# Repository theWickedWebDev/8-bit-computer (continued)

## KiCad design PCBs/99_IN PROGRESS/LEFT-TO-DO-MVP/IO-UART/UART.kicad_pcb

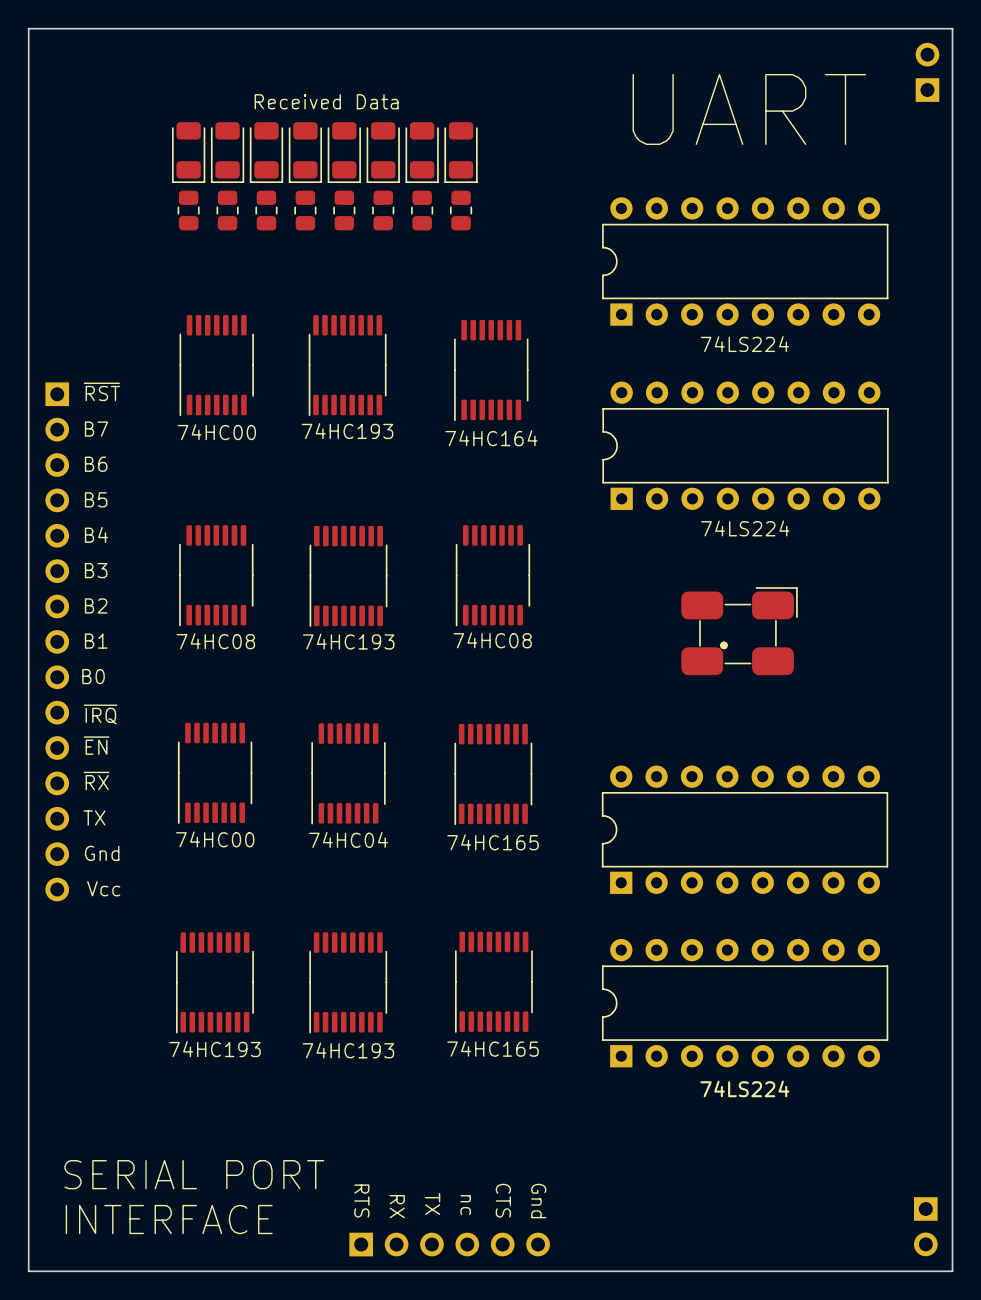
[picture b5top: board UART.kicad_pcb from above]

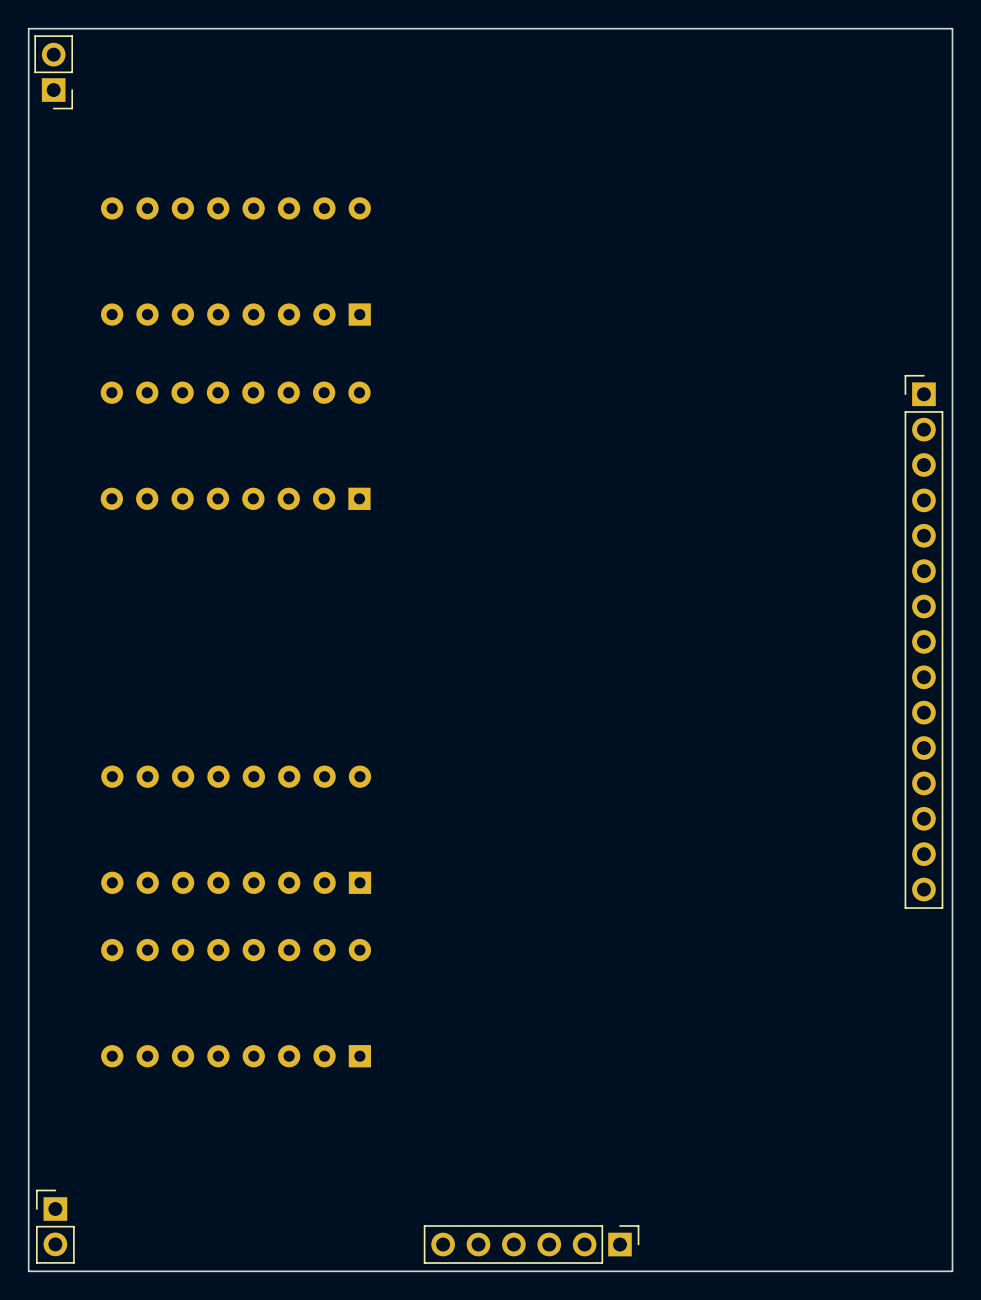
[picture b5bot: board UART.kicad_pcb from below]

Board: 4 copper layers, 66.3 x 89.2 mm, 37 parts (4 on the bottom side), 66 nets, no tracks yet.

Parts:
D1, D2, D3, D4, D5, D6, D7, D8: LED; LED_1206_3216Metric
J1: Conn_01x06; PinHeader_1x06_P2.54mm_Vertical
J2: Conn_01x15; PinHeader_1x15_P2.54mm_Vertical
J3, J4: Conn_01x02; PinHeader_1x02_P2.54mm_Vertical
R1, R2, R3, R4, R5, R6, R7, R8: 1kohm; R_0805_2012Metric
U1, U2, U3, U4: 74LS193; TSSOP-16_4.4x5mm_P0.65mm
U5, U14: 74LS08; TSSOP-14_4.4x5mm_P0.65mm
U6, U7: 74LS00; TSSOP-14_4.4x5mm_P0.65mm
U8: 74LS04; TSSOP-14_4.4x5mm_P0.65mm
U9: 74HC164; TSSOP-14_4.4x5mm_P0.65mm
U10, U11: 74LS165; TSSOP-16_4.4x5mm_P0.65mm
U12, U13, U15, U18: 74LS224; DIP-16_W7.62mm
Y1: Crystal_GND24; CFPS-72 SMD Clock

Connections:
/READ: U12.1 (OE), U12.15 (UNCK), U13.1 (OE), U13.15 (UNCK), U14.3
/TX0: D8.2 (A), U9.3 (Q0), U12.4 (D0)
/TX1: D7.2 (A), U9.4 (Q1), U12.5 (D1)
/TX2: D6.2 (A), U9.5 (Q2), U12.6 (D2)
/TX3: D5.2 (A), U9.6 (Q3), U12.7 (D3)
/TX4: D4.2 (A), U9.10 (Q4), U13.4 (D0)
/TX5: D3.2 (A), U9.11 (Q5), U13.5 (D1)
/TX6: D2.2 (A), U9.12 (Q6), U13.6 (D2)
/TX7: D1.2 (A), U9.13 (Q7), U13.7 (D3)
/TX_CLOCK: U2.7 (QD), U4.5 (UP), U6.10, U10.2 (CP), U11.2 (CP)
/TX_START: U4.11 (~LOAD), U6.3, U6.5, U10.1 (~PL), U11.1 (~PL), U15.1 (OE), U15.15 (UNCK), U18.1 (OE), U18.15 (UNCK)
/WRITE: U3.14 (CLR), U7.3, U7.4, U12.3 (LDCK), U13.3 (LDCK)
BUS0: J2.2, U12.13 (Q0), U15.4 (D0)
BUS1: J2.3, U12.12 (Q1), U15.5 (D1)
BUS2: J2.4, U12.11 (Q2), U15.6 (D2)
BUS3: J2.5, U12.10 (Q3), U15.7 (D3)
BUS4: J2.6, U13.13 (Q0), U18.4 (D0)
BUS5: J2.7, U13.12 (Q1), U18.5 (D1)
BUS6: J2.8, U13.11 (Q2), U18.6 (D2)
BUS7: J2.9, U13.10 (Q3), U18.7 (D3)
EN: U5.2, U8.6, U14.1
GND: J1.6, J2.14, R1.2, R2.2, R3.2, R4.2, R5.2, R6.2, R7.2, R8.2, U1.1 (B), U1.8 (GND), U1.10 (C), U1.14 (CLR), U2.1 (B), U2.8 (GND), U2.9 (D), U2.10 (C), U2.14 (CLR), U2.15 (A), U3.1 (B), U3.8 (GND), U3.9 (D), U3.10 (C), U3.15 (A), U4.1 (B), U4.8 (GND), U4.9 (D), U4.14 (CLR), U5.7 (GND), U5.12, U5.13, U6.7 (GND), U6.12, U6.13, U7.7 (GND), U7.9, U7.10, U7.12, U7.13, U8.7 (GND), U8.13, U9.7 (GND), U10.5 (D6), U10.8 (GND), U10.15 (~CE), U11.8 (GND), U11.15 (~CE), U12.8 (GND), U13.8 (GND), U14.7 (GND), U14.12, U14.13, U15.8 (GND), U18.8 (GND), Y1.2
unnamed: D1.1 (K), R1.1
unnamed: D2.1 (K), R2.1
unnamed: D3.1 (K), R3.1
unnamed: D4.1 (K), R4.1
unnamed: D5.1 (K), R5.1
unnamed: D6.1 (K), R6.1
unnamed: D7.1 (K), R7.1
unnamed: D8.1 (K), R8.1
unnamed: U1.4 (DOWN), U3.7 (QD), U9.8 (CP)
unnamed: U1.11 (~LOAD), U7.2, U7.6
unnamed: U1.13 (~BO), U7.1
unnamed: U4.12 (~CO), U6.4
unnamed: U5.5, U18.2 (IR)
unnamed: U5.8, U8.11
unnamed: U6.2, U6.8
unnamed: U8.1, U14.8
unnamed: U10.10 (DS), U11.9 (Q7)
unnamed: U12.2 (IR), U14.4
unnamed: U12.14 (OR), U14.9
unnamed: U13.2 (IR), U14.5
unnamed: U13.14 (OR), U14.10
unnamed: U5.4, U15.2 (IR)
unnamed: U5.9, U15.14 (OR)
unnamed: U5.10, U18.14 (OR)
RECEIVE_BYTE: J2.12, U8.4, U14.2
RX0: U10.4 (D5), U15.13 (Q0)
RX1: U10.3 (D4), U15.12 (Q1)
RX2: U10.14 (D3), U15.11 (Q2)
RX3: U10.13 (D2), U15.10 (Q3)
RX4: U10.12 (D1), U18.13 (Q0)
RX5: U10.11 (D0), U18.12 (Q1)
RX6: U11.6 (D7), U18.11 (Q2)
RX7: U11.5 (D6), U18.10 (Q3)
SER_CTS: J1.5, U14.6
SER_RTS: J1.1, U6.9, U8.10
SER_RX: J1.2, U10.9 (Q7)
SER_TX: J1.3, U7.5, U9.1 (DSA)
TF_DATA_READ: U6.1, U6.6
TRANSMIT_BYTE: J2.13, U5.1, U5.3, U8.8, U15.3 (LDCK), U18.3 (LDCK)
UART_CLOCK: U2.5 (UP), U3.5 (UP), Y1.3
VCC: J2.15, U1.5 (UP), U1.9 (D), U1.15 (A), U1.16 (VCC), U2.4 (DOWN), U2.11 (~LOAD), U2.16 (VCC), U3.4 (DOWN), U3.11 (~LOAD), U3.16 (VCC), U4.4 (DOWN), U4.10 (C), U4.15 (A), U4.16 (VCC), U5.14 (VCC), U6.14 (VCC), U7.14 (VCC), U8.14 (VCC), U9.2 (DSB), U9.9 (~MR), U9.14 (VCC), U10.6 (D7), U10.16 (VCC), U11.3 (D4), U11.4 (D5), U11.10 (DS), U11.11 (D0), U11.12 (D1), U11.13 (D2), U11.14 (D3), U11.16 (VCC), U12.16 (VCC), U13.16 (VCC), U14.14 (VCC), U15.16 (VCC), U18.16 (VCC), Y1.4
~EN: J2.11, U8.5
~RESET_BUFFERS: J2.1, U12.9 (~CLR), U13.9 (~CLR), U15.9 (~CLR), U18.9 (~CLR)
~RX_IRQ: J2.10, U8.2

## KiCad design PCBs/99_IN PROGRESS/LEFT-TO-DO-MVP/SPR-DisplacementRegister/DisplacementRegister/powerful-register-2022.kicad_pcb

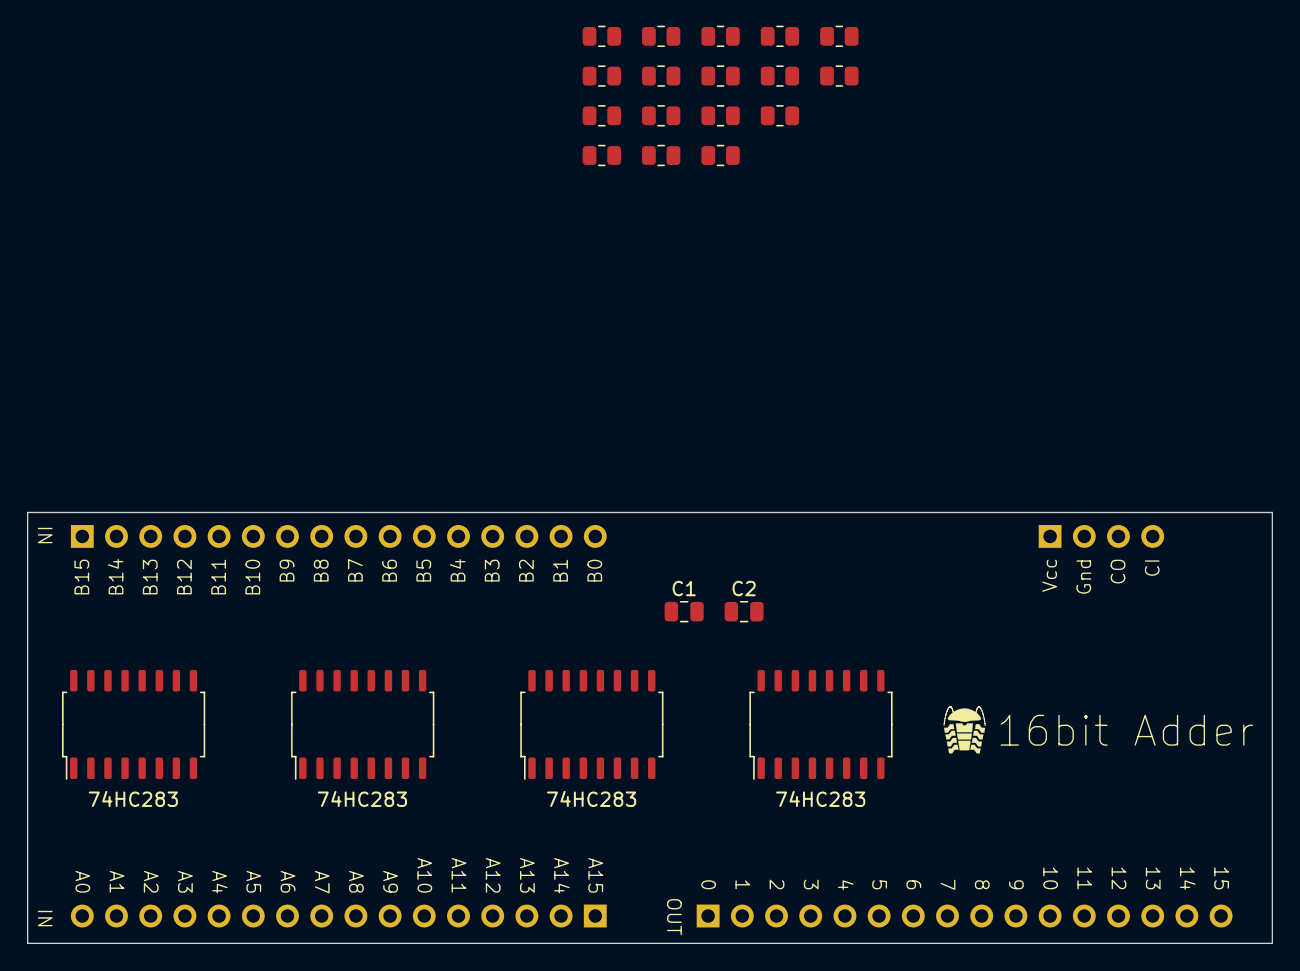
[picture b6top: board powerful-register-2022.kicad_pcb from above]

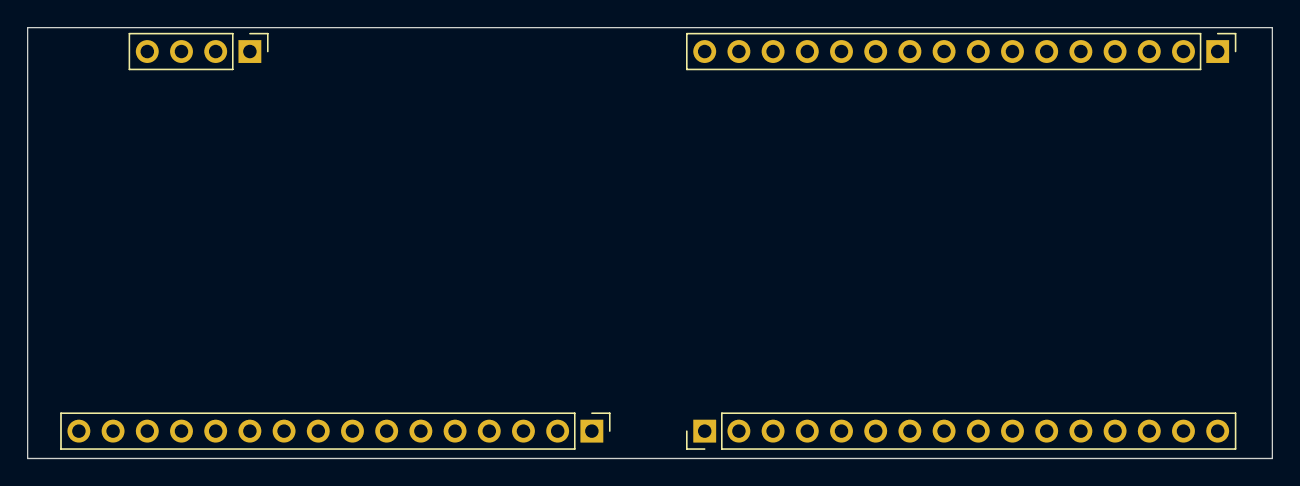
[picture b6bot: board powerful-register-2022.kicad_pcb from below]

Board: 4 copper layers, 92.5 x 32.0 mm, 27 parts (4 on the bottom side), 55 nets, no tracks yet.

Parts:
C1, C2: C; C_0805_2012Metric
J1: Conn_01x06; PinHeader_1x04_P2.54mm_Vertical
J2, J3, J4: Conn_01x16; PinHeader_1x16_P2.54mm_Vertical
R1, R2, R3, R4, R5, R6, R7, R8, R9, R10, R11, R12, R13, R14, R15, R16, R17: R_Small_US; R_0805_2012Metric
U1, U2, U3, U4: 74LS283; SOIC-16_4.55x10.3mm_P1.27mm

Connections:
A0: J2.16, U1.5 (A1)
A1: J2.15, U1.3 (A2)
A2: J2.14, U1.14 (A3)
A3: J2.13, U1.12 (A4)
A4: J2.12, U3.5 (A1)
A5: J2.11, U3.3 (A2)
A6: J2.10, U3.14 (A3)
A7: J2.9, U3.12 (A4)
A8: J2.8, U2.5 (A1)
A9: J2.7, U2.3 (A2)
A10: J2.6, U2.14 (A3)
A11: J2.5, U2.12 (A4)
A12: J2.4, U4.5 (A1)
A13: J2.3, U4.3 (A2)
A14: J2.2, U4.14 (A3)
A15: J2.1, U4.12 (A4)
B0: J4.16, R17.1, U1.6 (B1)
B1: J4.15, R16.1, U1.2 (B2)
B2: J4.14, R15.1, U1.15 (B3)
B3: J4.13, R14.1, U1.11 (B4)
B4: J4.12, R13.1, U3.6 (B1)
B5: J4.11, R12.1, U3.2 (B2)
B6: J4.10, R11.1, U3.15 (B3)
B7: J4.9, R10.1, U3.11 (B4)
B8: J4.8, R9.1, U2.6 (B1)
B9: J4.7, R8.1, U2.2 (B2)
B10: J4.6, R7.1, U2.15 (B3)
B11: J4.5, R6.1, U2.11 (B4)
B12: J4.4, R5.1, U4.6 (B1)
B13: J4.3, R4.1, U4.2 (B2)
B14: J4.2, R2.1, U4.15 (B3)
B15: J4.1, R1.1, U4.11 (B4)
CARRY_IN: J1.4, U1.7 (C0)
CARRY_OUT: J1.3, R3.1, U4.9 (C4)
GND: C1.2, C2.2, J1.2, R1.2, R2.2, R3.2, R4.2, R5.2, R6.2, R7.2, R8.2, R9.2, R10.2, R11.2, R12.2, R13.2, R14.2, R15.2, R16.2, R17.2, U1.8 (GND), U2.8 (GND), U3.8 (GND), U4.8 (GND)
unnamed: U1.9 (C4), U3.7 (C0)
unnamed: U2.7 (C0), U3.9 (C4)
unnamed: U2.9 (C4), U4.7 (C0)
Q0: J3.16, U1.4 (S1)
Q1: J3.15, U1.1 (S2)
Q2: J3.14, U1.13 (S3)
Q3: J3.13, U1.10 (S4)
Q4: J3.12, U3.4 (S1)
Q5: J3.11, U3.1 (S2)
Q6: J3.10, U3.13 (S3)
Q7: J3.9, U3.10 (S4)
Q8: J3.8, U2.4 (S1)
Q9: J3.7, U2.1 (S2)
Q10: J3.6, U2.13 (S3)
Q11: J3.5, U2.10 (S4)
Q12: J3.4, U4.4 (S1)
Q13: J3.3, U4.1 (S2)
Q14: J3.2, U4.13 (S3)
Q15: J3.1, U4.10 (S4)
VCC: C1.1, C2.1, J1.1, U1.16 (VCC), U2.16 (VCC), U3.16 (VCC), U4.16 (VCC)

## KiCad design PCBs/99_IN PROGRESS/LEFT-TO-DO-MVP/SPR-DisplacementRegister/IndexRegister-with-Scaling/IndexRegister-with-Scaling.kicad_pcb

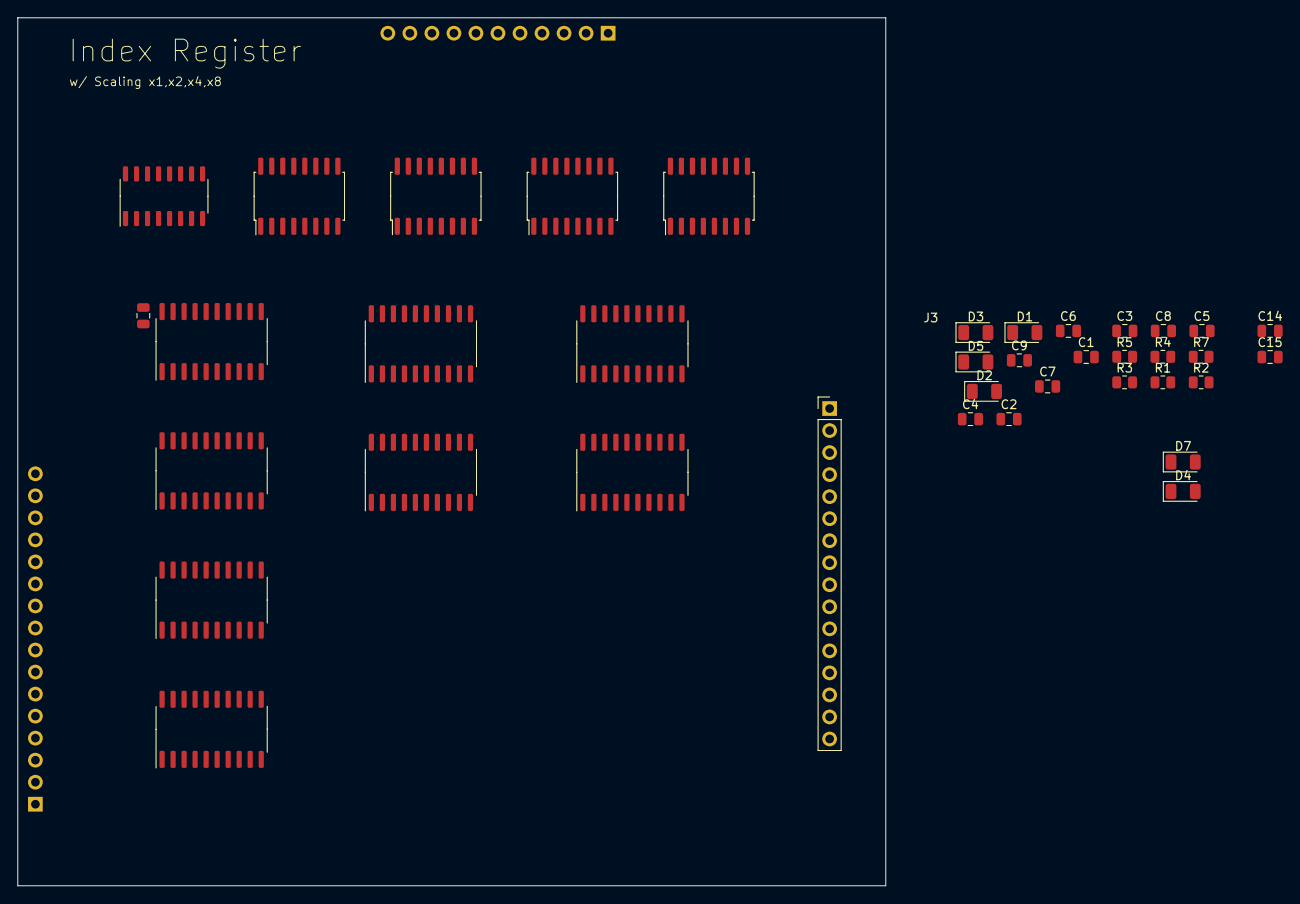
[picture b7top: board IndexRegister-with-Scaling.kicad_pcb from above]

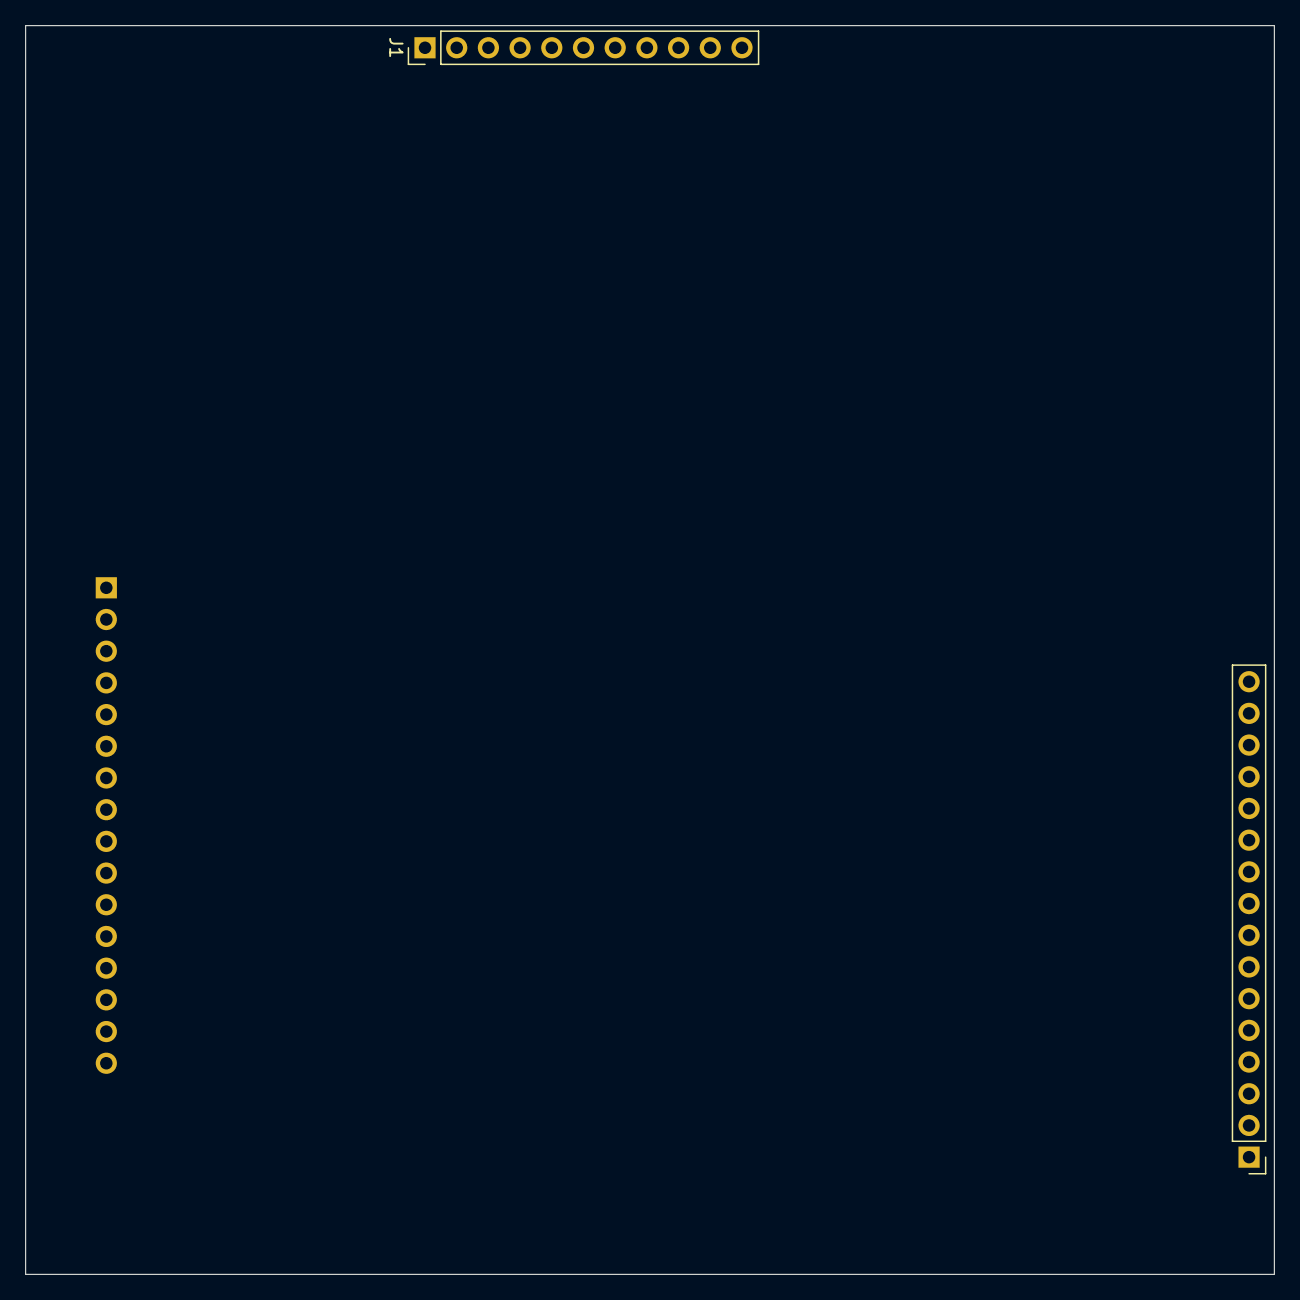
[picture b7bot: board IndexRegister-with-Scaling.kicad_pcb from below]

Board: 2 copper layers, 100.1 x 100.1 mm, 40 parts (2 on the bottom side), 75 nets, no tracks yet.

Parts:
C1, C2, C3, C4, C5, C6, C7, C8, C9: C; C_0805_2012Metric
C13, C14, C15: C_Small; C_0805_2012Metric
D1, D2, D3, D4, D5, D7: LED; LED_1206_3216Metric
J1: Conn_01x11; PinHeader_1x11_P2.54mm_Vertical
J2, J3: Conn_01x16; PinHeader_1x16_P2.54mm_Vertical
R1, R2, R3, R4, R5, R7: R_Small_US; R_0805_2012Metric
U1: 74LS139; SO-16_3.9x9.9mm_P1.27mm
U2, U3, U5, U6, U8, U9, U11, U12: 74LS245; SO-20_5.3x12.6mm_P1.27mm
U14, U15, U16, U17: 74LS193; SO-16_5.3x10.2mm_P1.27mm

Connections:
/Index Register/Q0: U2.2 (A0), U5.3 (A1), U8.4 (A2), U11.5 (A3), U14.3 (QA)
/Index Register/Q1: U2.3 (A1), U5.4 (A2), U8.5 (A3), U11.6 (A4), U14.2 (QB)
/Index Register/Q2: U2.4 (A2), U5.5 (A3), U8.6 (A4), U11.7 (A5), U14.6 (QC)
/Index Register/Q3: U2.5 (A3), U5.6 (A4), U8.7 (A5), U11.8 (A6), U14.7 (QD)
/Index Register/Q4: U2.6 (A4), U5.7 (A5), U8.8 (A6), U11.9 (A7), U15.3 (QA)
/Index Register/Q5: U2.7 (A5), U5.8 (A6), U8.9 (A7), U12.2 (A0), U15.2 (QB)
/Index Register/Q6: U2.8 (A6), U5.9 (A7), U9.2 (A0), U12.3 (A1), U15.6 (QC)
/Index Register/Q7: U2.9 (A7), U6.2 (A0), U9.3 (A1), U12.4 (A2), U15.7 (QD)
/Index Register/Q8: U3.2 (A0), U6.3 (A1), U9.4 (A2), U12.5 (A3), U16.3 (QA)
/Index Register/Q9: U3.3 (A1), U6.4 (A2), U9.5 (A3), U12.6 (A4), U16.2 (QB)
/Index Register/Q10: U3.4 (A2), U6.5 (A3), U9.6 (A4), U12.7 (A5), U16.6 (QC)
/Index Register/Q11: U3.5 (A3), U6.6 (A4), U9.7 (A5), U12.8 (A6), U16.7 (QD)
/Index Register/Q12: U3.6 (A4), U6.7 (A5), U9.8 (A6), U12.9 (A7), U17.3 (QA)
/Index Register/Q13: U3.7 (A5), U6.8 (A6), U9.9 (A7), U17.2 (QB)
/Index Register/Q14: U3.8 (A6), U6.9 (A7), U17.6 (QC)
/Index Register/Q15: U3.9 (A7), U17.7 (QD)
/Scaled Output/~SF1: U1.4 (O0), U2.19 (CE), U3.19 (CE)
/Scaled Output/~SF2: U1.5 (O1), U5.19 (CE), U6.19 (CE)
/Scaled Output/~SF4: U1.6 (O2), U8.19 (CE), U9.19 (CE)
/Scaled Output/~SF8: U1.7 (O3), U11.19 (CE), U12.19 (CE)
A0: J2.16, U14.15 (A)
A1: J2.15, U14.1 (B)
A2: J2.14, U14.10 (C)
A3: J2.13, U14.9 (D)
A4: J2.12, U15.15 (A)
A5: J2.11, U15.1 (B)
A6: J2.10, U15.10 (C)
A7: J2.9, U15.9 (D)
A8: J2.8, U16.15 (A)
A9: J2.7, U16.1 (B)
A10: J2.6, U16.10 (C)
A11: J2.5, U16.9 (D)
A12: J2.4, U17.15 (A)
A13: J2.3, U17.1 (B)
A14: J2.2, U17.10 (C)
A15: J2.1, U17.9 (D)
BO: J1.11, U17.13 (~BO)
CO: J1.10, U17.12 (~CO)
GND: C1.2, C2.2, C3.2, C4.2, C5.2, C6.2, C7.2, C8.2, C9.2, C13.2, C14.2, C15.2, J1.2, R1.2, R2.2, R3.2, R4.2, R5.2, R7.2, U1.8 (GND), U2.10 (GND), U3.10 (GND), U5.2 (A0), U5.10 (GND), U6.10 (GND), U8.2 (A0), U8.3 (A1), U8.10 (GND), U9.10 (GND), U11.2 (A0), U11.3 (A1), U11.4 (A2), U11.10 (GND), U12.10 (GND), U14.8 (GND), U15.8 (GND), U16.8 (GND), U17.8 (GND)
unnamed: D1.1 (K), R1.1
unnamed: D2.1 (K), R2.1
unnamed: D3.1 (K), R3.1
unnamed: D4.1 (K), R4.1
unnamed: D5.1 (K), R5.1
unnamed: D7.1 (K), R7.1
unnamed: U14.12 (~CO), U15.5 (UP)
unnamed: U14.13 (~BO), U15.4 (DOWN)
unnamed: U15.12 (~CO), U16.5 (UP)
unnamed: U15.13 (~BO), U16.4 (DOWN)
unnamed: U16.12 (~CO), U17.5 (UP)
unnamed: U16.13 (~BO), U17.4 (DOWN)
Q0: J3.16, U2.18 (B0), U5.18 (B0), U8.18 (B0), U11.18 (B0)
Q1: J3.15, U2.17 (B1), U5.17 (B1), U8.17 (B1), U11.17 (B1)
Q2: J3.14, U2.16 (B2), U5.16 (B2), U8.16 (B2), U11.16 (B2)
Q3: J3.13, U2.15 (B3), U5.15 (B3), U8.15 (B3), U11.15 (B3)
Q4: J3.12, U2.14 (B4), U5.14 (B4), U8.14 (B4), U11.14 (B4)
Q5: J3.11, U2.13 (B5), U5.13 (B5), U8.13 (B5), U11.13 (B5)
Q6: J3.10, U2.12 (B6), U5.12 (B6), U8.12 (B6), U11.12 (B6)
Q7: J3.9, U2.11 (B7), U5.11 (B7), U8.11 (B7), U11.11 (B7)
Q8: J3.8, U3.18 (B0), U6.18 (B0), U9.18 (B0), U12.18 (B0)
Q9: J3.7, U3.17 (B1), U6.17 (B1), U9.17 (B1), U12.17 (B1)
Q10: J3.6, U3.16 (B2), U6.16 (B2), U9.16 (B2), U12.16 (B2)
Q11: J3.5, U3.15 (B3), U6.15 (B3), U9.15 (B3), U12.15 (B3)
Q12: J3.4, U3.14 (B4), U6.14 (B4), U9.14 (B4), U12.14 (B4)
Q13: J3.3, U3.13 (B5), U6.13 (B5), U9.13 (B5), U12.13 (B5)
Q14: J3.2, U3.12 (B6), U6.12 (B6), U9.12 (B6), U12.12 (B6)
Q15: J3.1, U3.11 (B7), U6.11 (B7), U9.11 (B7), U12.11 (B7)
RESET: J1.3, U14.14 (CLR), U15.14 (CLR), U16.14 (CLR), U17.14 (CLR)
VCC: C1.1, C2.1, C3.1, C4.1, C5.1, C6.1, C7.1, C8.1, C9.1, C13.1, C14.1, C15.1, J1.1, U1.15 (E), U1.16 (VCC), U2.1 (A->B), U2.20 (VCC), U3.1 (A->B), U3.20 (VCC), U5.1 (A->B), U5.20 (VCC), U6.1 (A->B), U6.20 (VCC), U8.1 (A->B), U8.20 (VCC), U9.1 (A->B), U9.20 (VCC), U11.1 (A->B), U11.20 (VCC), U12.1 (A->B), U12.20 (VCC), U14.16 (VCC), U15.16 (VCC), U16.16 (VCC), U17.16 (VCC)
~INDEX_C0: D4.2 (A), J1.7, U1.3 (A1)
~INDEX_C1: D5.2 (A), J1.8, U1.2 (A0)
~INDEX_DEC: D1.2 (A), J1.4, U14.4 (DOWN)
~INDEX_INC: D2.2 (A), J1.5, U14.5 (UP)
~INDEX_LOAD: D3.2 (A), J1.6, U14.11 (~LOAD), U15.11 (~LOAD), U16.11 (~LOAD), U17.11 (~LOAD)
~INDEX_OE: D7.2 (A), J1.9, U1.1 (E)

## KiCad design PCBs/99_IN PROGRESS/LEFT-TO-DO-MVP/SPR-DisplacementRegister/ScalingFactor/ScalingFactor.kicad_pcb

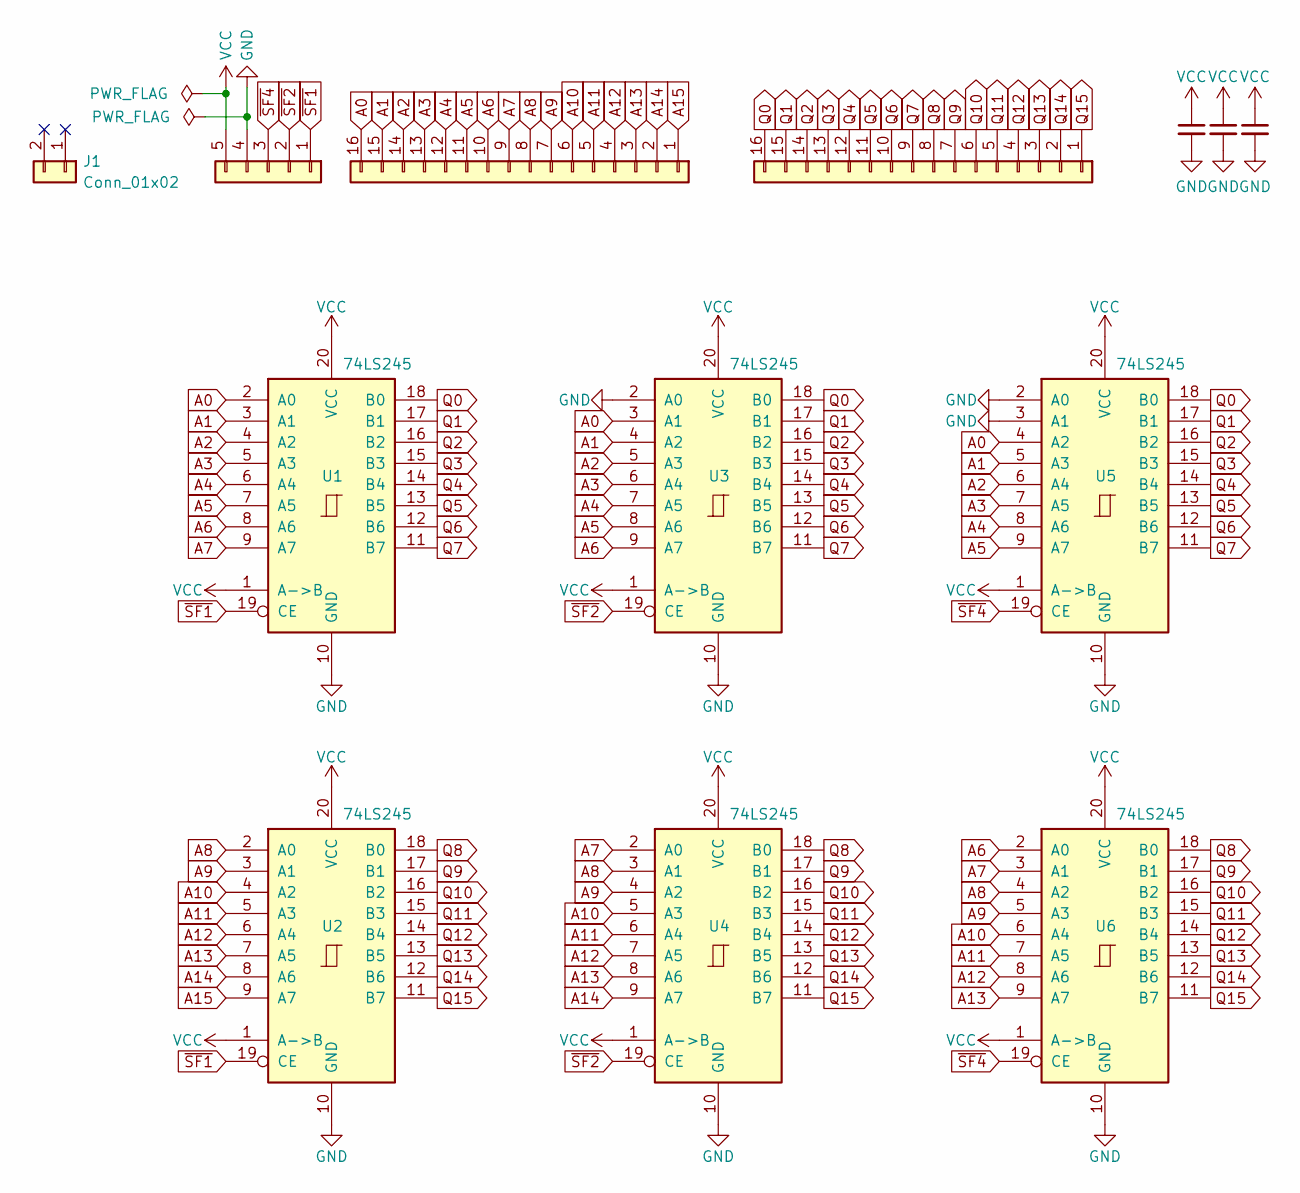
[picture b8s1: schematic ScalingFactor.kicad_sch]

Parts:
C1, C2, C3: C_Small; C_0805_2012Metric
J1: Conn_01x02; PinHeader_1x02_P2.54mm_Vertical
J2: Conn_01x05; PinHeader_1x05_P2.54mm_Vertical
J3, J4: Conn_01x16; PinHeader_1x16_P2.54mm_Vertical
U1, U2, U3, U4, U5, U6: 74LS245; SO-20_5.3x12.6mm_P1.27mm

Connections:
A0: J3.16, U1.2 (A0), U3.3 (A1), U5.4 (A2)
A1: J3.15, U1.3 (A1), U3.4 (A2), U5.5 (A3)
A2: J3.14, U1.4 (A2), U3.5 (A3), U5.6 (A4)
A3: J3.13, U1.5 (A3), U3.6 (A4), U5.7 (A5)
A4: J3.12, U1.6 (A4), U3.7 (A5), U5.8 (A6)
A5: J3.11, U1.7 (A5), U3.8 (A6), U5.9 (A7)
A6: J3.10, U1.8 (A6), U3.9 (A7), U6.2 (A0)
A7: J3.9, U1.9 (A7), U4.2 (A0), U6.3 (A1)
A8: J3.8, U2.2 (A0), U4.3 (A1), U6.4 (A2)
A9: J3.7, U2.3 (A1), U4.4 (A2), U6.5 (A3)
A10: J3.6, U2.4 (A2), U4.5 (A3), U6.6 (A4)
A11: J3.5, U2.5 (A3), U4.6 (A4), U6.7 (A5)
A12: J3.4, U2.6 (A4), U4.7 (A5), U6.8 (A6)
A13: J3.3, U2.7 (A5), U4.8 (A6), U6.9 (A7)
A14: J3.2, U2.8 (A6), U4.9 (A7)
A15: J3.1, U2.9 (A7)
GND: C1.2, C2.2, C3.2, J2.4, U1.10 (GND), U2.10 (GND), U3.2 (A0), U3.10 (GND), U4.10 (GND), U5.2 (A0), U5.3 (A1), U5.10 (GND), U6.10 (GND)
Q0: J4.16, U1.18 (B0), U3.18 (B0), U5.18 (B0)
Q1: J4.15, U1.17 (B1), U3.17 (B1), U5.17 (B1)
Q2: J4.14, U1.16 (B2), U3.16 (B2), U5.16 (B2)
Q3: J4.13, U1.15 (B3), U3.15 (B3), U5.15 (B3)
Q4: J4.12, U1.14 (B4), U3.14 (B4), U5.14 (B4)
Q5: J4.11, U1.13 (B5), U3.13 (B5), U5.13 (B5)
Q6: J4.10, U1.12 (B6), U3.12 (B6), U5.12 (B6)
Q7: J4.9, U1.11 (B7), U3.11 (B7), U5.11 (B7)
Q8: J4.8, U2.18 (B0), U4.18 (B0), U6.18 (B0)
Q9: J4.7, U2.17 (B1), U4.17 (B1), U6.17 (B1)
Q10: J4.6, U2.16 (B2), U4.16 (B2), U6.16 (B2)
Q11: J4.5, U2.15 (B3), U4.15 (B3), U6.15 (B3)
Q12: J4.4, U2.14 (B4), U4.14 (B4), U6.14 (B4)
Q13: J4.3, U2.13 (B5), U4.13 (B5), U6.13 (B5)
Q14: J4.2, U2.12 (B6), U4.12 (B6), U6.12 (B6)
Q15: J4.1, U2.11 (B7), U4.11 (B7), U6.11 (B7)
VCC: C1.1, C2.1, C3.1, J2.5, U1.1 (A->B), U1.20 (VCC), U2.1 (A->B), U2.20 (VCC), U3.1 (A->B), U3.20 (VCC), U4.1 (A->B), U4.20 (VCC), U5.1 (A->B), U5.20 (VCC), U6.1 (A->B), U6.20 (VCC)
~SF1: J2.1, U1.19 (CE), U2.19 (CE)
~SF2: J2.2, U3.19 (CE), U4.19 (CE)
~SF4: J2.3, U5.19 (CE), U6.19 (CE)

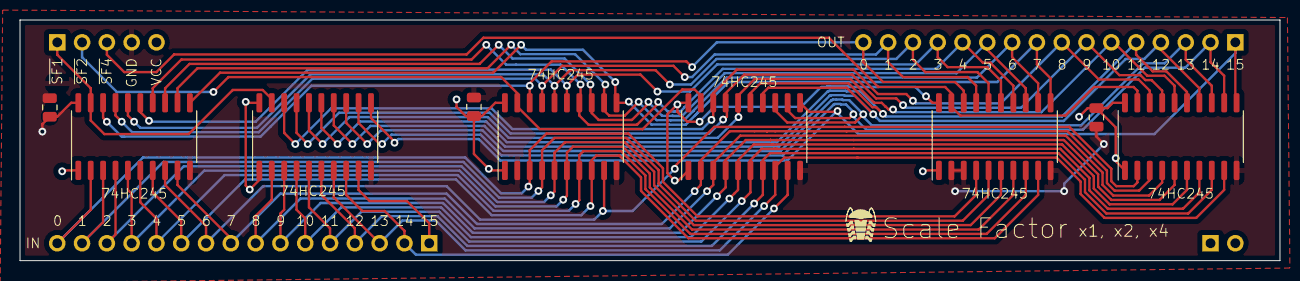
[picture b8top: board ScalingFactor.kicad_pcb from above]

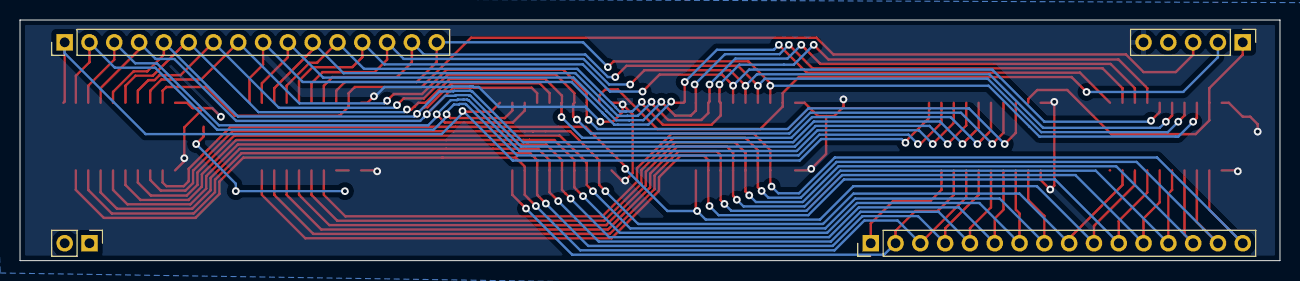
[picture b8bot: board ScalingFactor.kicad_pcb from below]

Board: 2 copper layers, 129.0 x 24.6 mm, 13 parts (4 on the bottom side), 37 nets.
